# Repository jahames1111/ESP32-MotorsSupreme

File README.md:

# ESP32-MotorsSupreme

A huge motor driver board based on ESP32 featuring capacitors and motor/servo output pins everywhere. 
This project was created mainly for testing old servos that I have lying around at the beginning of a new project to see what works or not.
I'll use it because I have dozens of servos and don't know whether they work. This will let me test them with certainty.
I put a  lot of thought into this project, choosing the easiest-to-solder chips, looking up the right resistor and capacitor values, and finding the best ESP32 chip. I also made sure to select parts on a low budget, but they still worked and were reliable. I also had to carefully model the digital representation of the board to base my case on. 

## Features

- 8 DRV8833 motor drivers for 16 2-directional PWM motor outputs
- 2 PCA9685 chips for servo outputs and one pin of the DRV channels (the other is the ESP pin)
- 16 ESP32-S2 WROVER pins for DRV direction control
- Built for testing nonworking motors and servos

## BOM
| Designator | Footprint / Package | Quantity | Value / Description | LCSC Part # / MPN | Sourcing Resource Link |
| :--- | :--- | :---: | :--- | :---: | :--- |
| **U1** | VFQFN-56-EP | 1 | ESP32-S2-WROVER Module | C7274976 | [LCSC Product Page](https://lcsc.com) |
| **U6, U7, U8, U9, U10, U11, U12, U13** | HTSSOP-16-1EP | 8 | DRV8833PWPR Motor Driver IC | C50506 | [LCSC Product Page](https://www.lcsc.com/product-detail/C50506.html) |
| **U2, U5** | TSSOP-28 | 2 | PCA9685PW,118 PWM Driver IC | C2678753 | [LCSC Product Page](https://lcsc.com) |
| **U3** | SOT-23-5L | 1 | HMIC5219-3.3YM5 LDO Regulator | C41381680 | [LCSC Product Page](https://lcsc.com) |
| **J22** | SMD / TYPE-C-31-M-12 | 1 | USB-C (USB TYPE-C) Receptacle | C165948 | [LCSC Product Page](https://lcsc.com) |
| **D1, D2** | SMA (DO-214AC) | 2 | SS14 40V 1A Schottky Diode | C2480 | [LCSC Product Page](https://lcsc.com) |
| **SW1, SW2** | Through Hole (6x6mm) | 2 | TS665CJ Tactile Switch SPST 5mm | C393938 | [LCSC Product Page](https://lcsc.com) |
| **C1 to C19** | 1206 | 19 | CL31A106KBHNNNE 10uF 50V Ceramic | C13585 | [LCSC Product Page](https://lcsc.com) |
| **R1, R2** | 1206 | 2 | FRC1206F4701TS 4.7kΩ ±1% Resistor | C2907387 | [LCSC Product Page](https://lcsc.com) |
| **R3, R4, R5, R6** | 1206 | 4 | FRC1206J512 TS 5.1kΩ ±5% Resistor | C2907509 | [LCSC Product Page](https://lcsc.com) |
| **J3 to J18** | PinHeader_1x02_P2.54mm_Vertical | 16 | 2-Pin Vertical Male Pin Header Strip | — | *Standard 2.54mm pitch hardware connectors* |
| **J19, J20, J21** | PinHeader_1x16_P2.54mm_Vertical | 3 | 16-Pin Vertical Male Pin Header Strip | — | *Standard 2.54mm pitch hardware connectors* |
| **J1** | SolderWire-1sqmm (D1.4mm) | 1 | BAT- Wire Connection Pad | — | *Direct wire Solder Pad (No Component)* |
| **J2** | SolderWire-1sqmm (D1.4mm) | 1 | BAT+ Wire Connection Pad | — | *Direct wire Solder Pad (No Component)* |

**Total Cost: \$58.83 USD**

Assembly
The 3d printed frame will fit perfectly around the board; it may need some sanding if the walls were too thick. After that, upload the code through the Arduino IDE after downloading the ESP32 Servo and Wire (automatically included) libraries. It will automatically oscillate the motors and the servos so you can test any old ones that you aren't sure are working.

Wiring (close-up detailed schematic screenshots)

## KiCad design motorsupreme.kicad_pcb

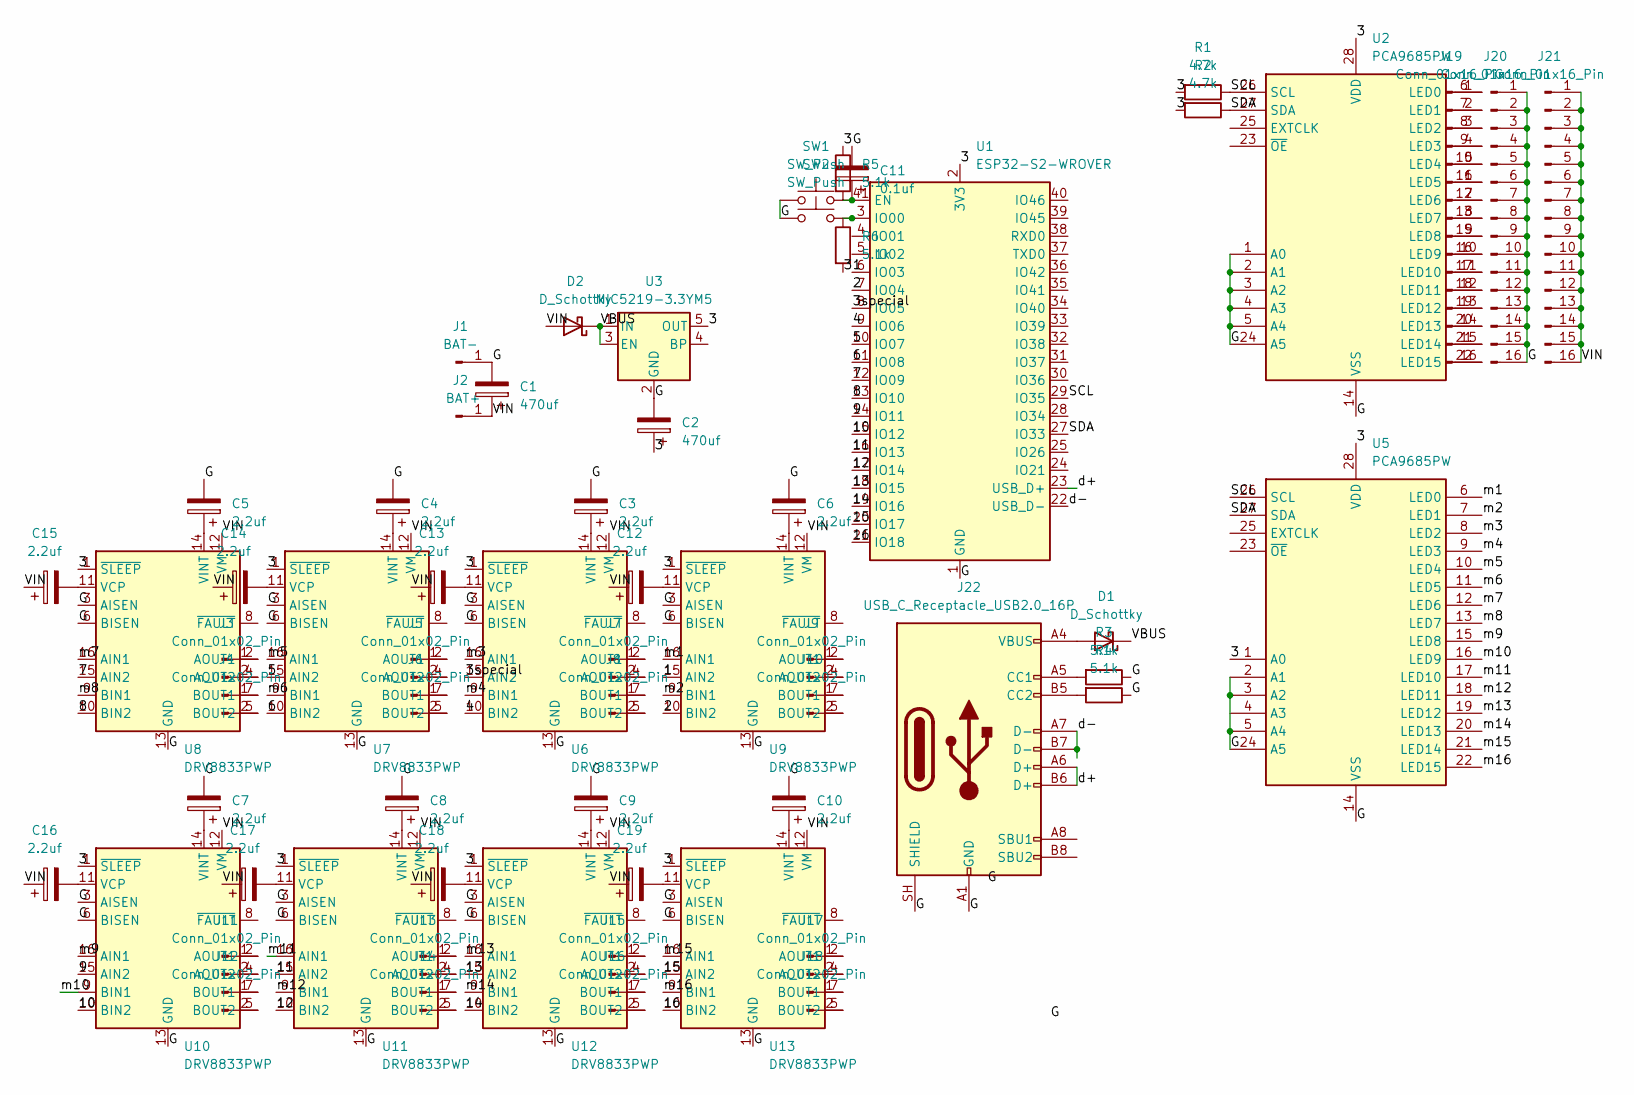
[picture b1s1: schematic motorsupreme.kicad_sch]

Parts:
C1: 470uf; CP_Radial_D8.0mm_P3.50mm
C2: 470uf; C_1206_3216Metric
C3, C4, C5, C6, C7, C8, C9, C10, C12, C13, C14, C15, C16, C17, C18, C19: 2.2uf; C_1206_3216Metric
C11: 0.1uf; C_1206_3216Metric
D1, D2: D_Schottky; D_SMA
J1: BAT-; SolderWire-1sqmm_1x01_D1.4mm_OD3.9mm
J2: BAT+; SolderWire-1sqmm_1x01_D1.4mm_OD3.9mm
J3, J4, J5, J6, J7, J8, J9, J10, J11, J12, J13, J14, J15, J16, J17, J18: Conn_01x02_Pin; PinHeader_1x02_P2.54mm_Vertical
J19, J20, J21: Conn_01x16_Pin; PinHeader_1x16_P2.54mm_Vertical
J22: USB_C_Receptacle_USB2.0_16P; USB_C_Receptacle_HRO_TYPE-C-31-M-12
R1, R2: 4.7k; R_1206_3216Metric
R3, R4, R5, R6: 5.1k; R_1206_3216Metric
SW1, SW2: SW_Push; SW_PUSH_6mm
U1: ESP32-S2-WROVER
U2, U5: PCA9685PW; TSSOP-28_4.4x9.7mm_P0.65mm
U3: MIC5219-3.3YM5; SOT-23-5
U6, U7, U8, U9, U10, U11, U12, U13: DRV8833PWP; HTSSOP-16-1EP_4.4x5mm_P0.65mm_EP3.4x5mm_Mask2.46x2.31mm_The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

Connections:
/1: U1.6 (IO03), U9.15 (AIN2)
/2: U1.7 (IO04), U9.10 (BIN2)
/3: C2.1, R1.2, R2.2, R5.1, R6.2, U1.2 (3V3), U2.28 (VDD), U3.5 (OUT), U5.1 (A0), U5.28 (VDD), U6.1 (~SLEEP), U7.1 (~SLEEP), U8.1 (~SLEEP), U9.1 (~SLEEP), U10.1 (~SLEEP), U11.1 (~SLEEP), U12.1 (~SLEEP), U13.1 (~SLEEP)
/3special: U1.8 (IO05), U6.15 (AIN2)
/4: U1.9 (IO06), U6.10 (BIN2)
/5: U1.10 (IO07), U7.15 (AIN2)
/6: U1.11 (IO08), U7.10 (BIN2)
/7: U1.12 (IO09), U8.15 (AIN2)
/8: U1.13 (IO10), U8.10 (BIN2)
/9: U1.14 (IO11), U10.15 (AIN2)
/10: U1.15 (IO12), U10.10 (BIN2)
/11: U1.16 (IO13), U11.15 (AIN2)
/12: U1.17 (IO14), U11.10 (BIN2)
/13: U1.18 (IO15), U12.15 (AIN2)
/14: U1.19 (IO16), U12.10 (BIN2)
/15: U1.20 (IO17), U13.15 (AIN2)
/16: U1.21 (IO18), U13.10 (BIN2)
/G: C1.2, C2.2, C3.2, C4.2, C5.2, C6.2, C7.2, C8.2, C9.2, C10.2, C11.2, J1.1 (Pin_1_1), J20.1, J20.2, J20.3, J20.4, J20.5, J20.6, J20.7, J20.8, J20.9, J20.10, J20.11, J20.12, J20.13, J20.14, J20.15, J20.16, J22.A1 (GND), J22.A12 (GND), J22.B1 (GND), J22.B12 (GND), J22.SH (SHIELD), R3.1, R4.1, SW1.1, SW2.1, U1.1 (GND), U1.26 (GND), U1.42 (GND), U1.43 (GND), U2.1 (A0), U2.2 (A1), U2.3 (A2), U2.4 (A3), U2.5 (A4), U2.14 (VSS), U2.24 (A5), U3.2 (GND), U5.2 (A1), U5.3 (A2), U5.5 (A4), U5.14 (VSS), U5.24 (A5), U6.3 (AISEN), U6.6 (BISEN), U6.13 (GND), U6.17 (GND), U7.3 (AISEN), U7.6 (BISEN), U7.13 (GND), U7.17 (GND), U8.3 (AISEN), U8.6 (BISEN), U8.13 (GND), U8.17 (GND), U9.3 (AISEN), U9.6 (BISEN), U9.13 (GND), U9.17 (GND), U10.3 (AISEN), U10.6 (BISEN), U10.13 (GND), U10.17 (GND), U11.3 (AISEN), U11.6 (BISEN), U11.13 (GND), U11.17 (GND), U12.3 (AISEN), U12.6 (BISEN), U12.13 (GND), U12.17 (GND), U13.3 (AISEN), U13.6 (BISEN), U13.13 (GND), U13.17 (GND)
/SCL: R1.1, U1.29 (IO35), U2.26 (SCL), U5.26 (SCL)
/SDA: R2.1, U1.27 (IO33), U2.27 (SDA), U5.27 (SDA)
/VBUS: D1.1 (K), D2.1 (K), U3.1 (IN), U3.3 (EN)
/VIN: C1.1, C12.1, C13.1, C14.1, C15.1, C16.1, C17.1, C18.1, C19.1, D2.2 (A), J2.1 (Pin_1_1), J21.1, J21.2, J21.3, J21.4, J21.5, J21.6, J21.7, J21.8, J21.9, J21.10, J21.11, J21.12, J21.13, J21.14, J21.15, J21.16, U6.12 (VM), U7.12 (VM), U8.12 (VM), U9.12 (VM), U10.12 (VM), U11.12 (VM), U12.12 (VM), U13.12 (VM)
/d+: J22.A6 (D+), J22.B6 (D+), U1.23 (USB_D+)
/d-: J22.A7 (D-), J22.B7 (D-), U1.22 (USB_D-)
/m1: U5.6 (LED0), U9.16 (AIN1)
/m2: U5.7 (LED1), U9.9 (BIN1)
/m3: U5.8 (LED2), U6.16 (AIN1)
/m4: U5.9 (LED3), U6.9 (BIN1)
/m5: U5.10 (LED4), U7.16 (AIN1)
/m6: U5.11 (LED5), U7.9 (BIN1)
/m7: U5.12 (LED6), U8.16 (AIN1)
/m8: U5.13 (LED7), U8.9 (BIN1)
/m9: U5.15 (LED8), U10.16 (AIN1)
/m10: U5.16 (LED9), U10.9 (BIN1)
/m11: U5.17 (LED10), U11.16 (AIN1)
/m12: U5.18 (LED11), U11.9 (BIN1)
/m13: U5.19 (LED12), U12.16 (AIN1)
/m14: U5.20 (LED13), U12.9 (BIN1)
/m15: U5.21 (LED14), U13.16 (AIN1)
/m16: U5.22 (LED15), U13.9 (BIN1)
unnamed: D1.2 (A), J22.A4 (VBUS), J22.A9 (VBUS), J22.B4 (VBUS), J22.B9 (VBUS)
unnamed: J3.1, U8.2 (AOUT1)
unnamed: J3.2, U8.4 (AOUT2)
unnamed: J4.1, U8.7 (BOUT1)
unnamed: J4.2, U8.5 (BOUT2)
unnamed: J5.1, U7.2 (AOUT1)
unnamed: J5.2, U7.4 (AOUT2)
unnamed: J6.1, U7.7 (BOUT1)
unnamed: J6.2, U7.5 (BOUT2)
unnamed: J7.1, U6.2 (AOUT1)
unnamed: J7.2, U6.4 (AOUT2)
unnamed: J8.1, U6.7 (BOUT1)
unnamed: J8.2, U6.5 (BOUT2)
unnamed: J9.1, U9.2 (AOUT1)
unnamed: J9.2, U9.4 (AOUT2)
unnamed: J10.1, U9.7 (BOUT1)
unnamed: J10.2, U9.5 (BOUT2)
unnamed: J11.1, U10.2 (AOUT1)
unnamed: J11.2, U10.4 (AOUT2)
unnamed: J12.1, U10.7 (BOUT1)
unnamed: J12.2, U10.5 (BOUT2)
unnamed: J13.1, U11.2 (AOUT1)
unnamed: J13.2, U11.4 (AOUT2)
unnamed: J14.1, U11.7 (BOUT1)
unnamed: J14.2, U11.5 (BOUT2)
unnamed: J15.1, U12.2 (AOUT1)
unnamed: J15.2, U12.4 (AOUT2)
unnamed: J16.1, U12.7 (BOUT1)
unnamed: J16.2, U12.5 (BOUT2)
unnamed: J17.1, U13.2 (AOUT1)
unnamed: J17.2, U13.4 (AOUT2)
unnamed: J18.1, U13.7 (BOUT1)
unnamed: J18.2, U13.5 (BOUT2)
unnamed: J19.1, U2.6 (LED0)
unnamed: J19.2, U2.7 (LED1)
unnamed: J19.3, U2.8 (LED2)
unnamed: J19.4, U2.9 (LED3)
unnamed: J19.5, U2.10 (LED4)
unnamed: J19.6, U2.11 (LED5)
unnamed: J19.7, U2.12 (LED6)
unnamed: J19.8, U2.13 (LED7)
unnamed: J19.9, U2.15 (LED8)
unnamed: J19.10, U2.16 (LED9)
unnamed: J19.11, U2.17 (LED10)
unnamed: J19.12, U2.18 (LED11)
unnamed: J19.13, U2.19 (LED12)
unnamed: J19.14, U2.20 (LED13)
unnamed: J19.15, U2.21 (LED14)
unnamed: J19.16, U2.22 (LED15)
unnamed: J22.A5 (CC1), R3.2
unnamed: J22.B5 (CC2), R4.2
unnamed: C11.1, R5.2, SW1.2, U1.41 (EN)
unnamed: R6.1, SW2.2, U1.3 (IO00)
unnamed: C13.2, U6.11 (VCP)
unnamed: C3.1, U6.14 (VINT)
unnamed: C14.2, U7.11 (VCP)
unnamed: C4.1, U7.14 (VINT)
unnamed: C15.2, U8.11 (VCP)
unnamed: C5.1, U8.14 (VINT)
unnamed: C12.2, U9.11 (VCP)
unnamed: C6.1, U9.14 (VINT)
unnamed: C16.2, U10.11 (VCP)
unnamed: C7.1, U10.14 (VINT)
unnamed: C17.2, U11.11 (VCP)
unnamed: C8.1, U11.14 (VINT)
unnamed: C18.2, U12.11 (VCP)
unnamed: C9.1, U12.14 (VINT)
unnamed: C19.2, U13.11 (VCP)
unnamed: C10.1, U13.14 (VINT)

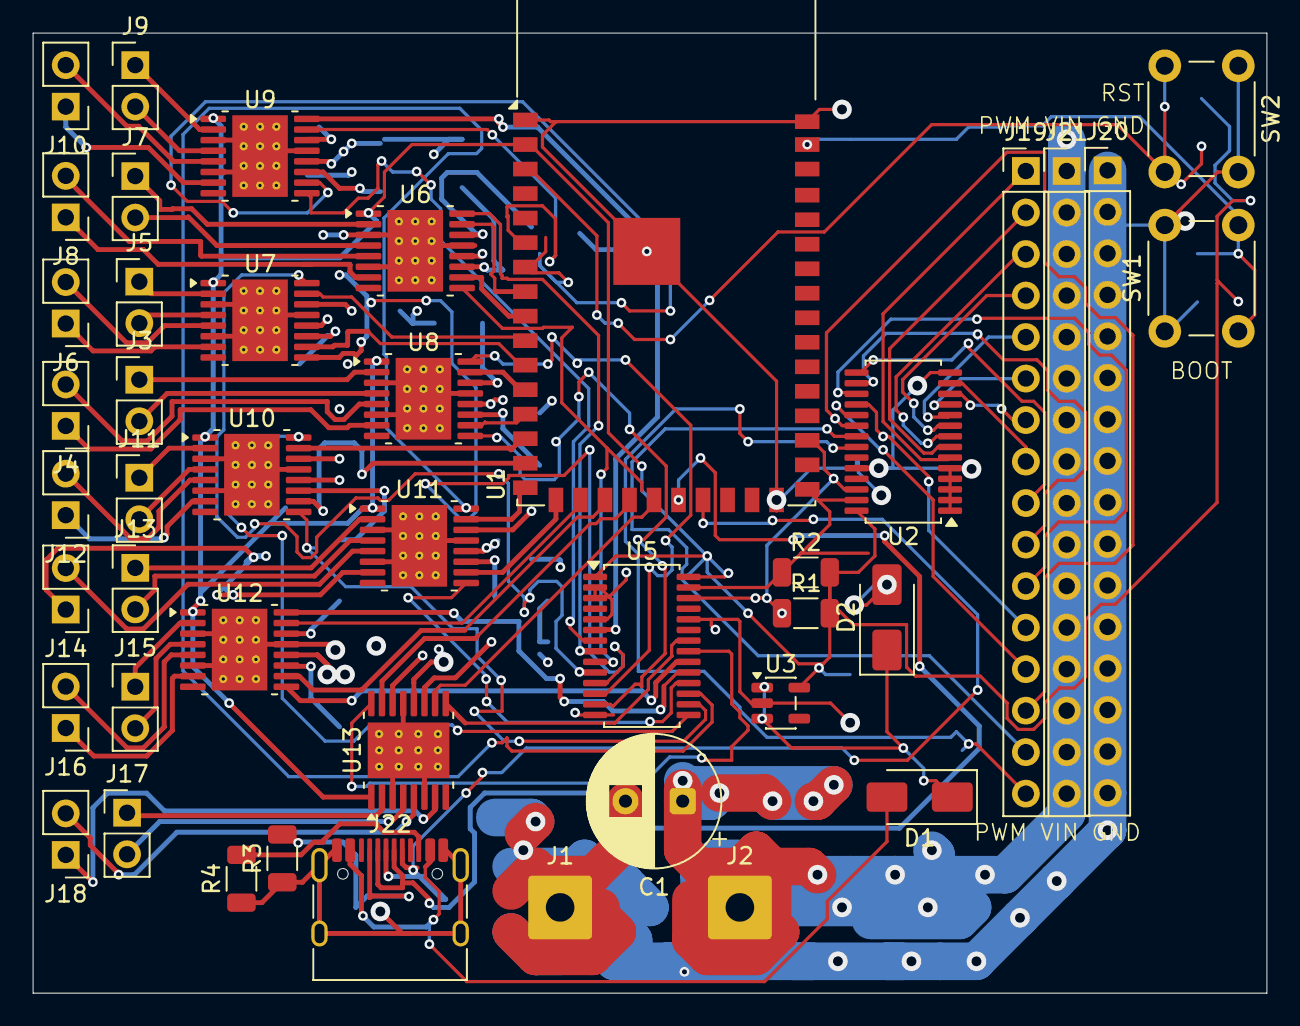
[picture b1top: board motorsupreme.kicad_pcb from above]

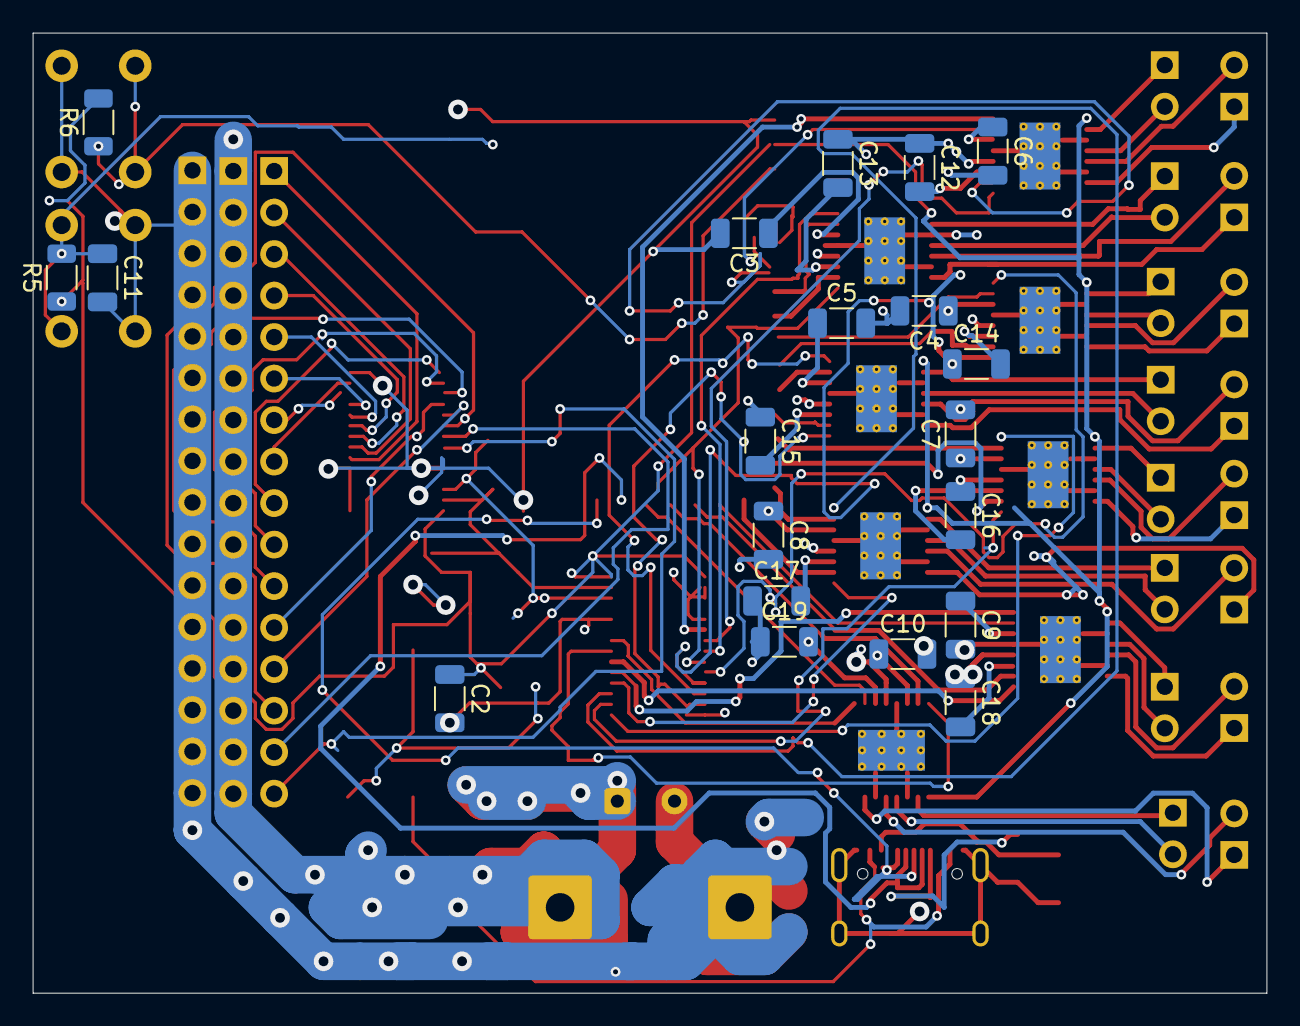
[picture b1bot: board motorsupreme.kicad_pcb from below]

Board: 4 copper layers, 75.5 x 58.8 mm, 63 parts (20 on the bottom side), 109 nets.

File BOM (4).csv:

Designator,Footprint,Quantity,Value,LCSC Part #
C1,CP_Radial_D8.0mm_P3.50mm,1,470uf,
"C10, C12, C13, C14, C15, C16, C17, C18, C19, C3, C4, C5, C6, C7, C8, C9",1206,16,2.2uf,
C11,1206,1,0.1uf,
C2,1206,1,470uf,
"D1, D2",D_SMA,2,D_Schottky,
J1,SolderWire-1sqmm_1x01_D1.4mm_OD3.9mm,1,BAT-,N/A
"J10, J11, J12, J13, J14, J15, J16, J17, J18, J3, J4, J5, J6, J7, J8, J9",PinHeader_1x02_P2.54mm_Vertical,16,Conn_01x02_Pin,
"J19, J20, J21",PinHeader_1x16_P2.54mm_Vertical,3,Conn_01x16_Pin,
J2,SolderWire-1sqmm_1x01_D1.4mm_OD3.9mm,1,BAT+,N/A
J22,USB_C_Receptacle_HRO_TYPE-C-31-M-12,1,USB_C_Receptacle_USB2.0_16P,
"R1, R2",1206,2,4.7k,
"R3, R4, R5, R6",1206,4,5.1k,
"SW1, SW2",SW_PUSH_6mm,2,SW_Push,
U1,ESP32-S2-WROVER,1,ESP32-S2-WROVER,C6616601
"U10, U11, U12, U13, U6, U7, U8, U9",HTSSOP-16-1EP_4.4x5mm_P0.65mm_EP3.4x5mm_Mask2.46x2.31mm_ThermalVias,8,DRV8833PWP,C50506
"U2, U5",TSSOP-28_4.4x9.7mm_P0.65mm,2,PCA9685PW,C92206
U3,SOT-23-5,1,MIC5219-3.3YM5,C29613
